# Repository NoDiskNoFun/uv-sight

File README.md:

# Anchored

**Anchored** is a bow sight add-on: automatic UV illumination, cant indicator and shot counter for a compound bow hunting sight. **Nocked** is its companion app, as a web app in this repository and as a native Android app in [uv-sight-android](https://github.com/NoDiskNoFun/uv-sight-android). The repositories keep their original name `uv-sight`.

> **Disclaimer: AI-generated project**
>
> The firmware, the web app, this README and the hardware design (part selection and wiring) were created with **Claude**, an AI assistant by Anthropic, in a conversation with the project owner.
>
> | | |
> |---|---|
> | Model | Claude Opus 5.5 (Anthropic) |
> | Interface | claude.ai, chat with code execution and web search |
> | Period | 23 September 2026, finished on 25 September 2026; reviewed and extended on 30 September 2026 |
> | Human role | Requirements and feature decisions, choice and purchase of parts, soldering and assembly, compiling and flashing, testing on the real bow, bug reports |
> | AI role | Part selection and wiring, all firmware and app code, protocol design, research of datasheets and pinouts, documentation |
> | Testing by the AI | Syntax and type checks of the firmware against mock libraries, JSON validity checks, and an end-to-end test of the app in Chromium against the firmware running natively with mocked IMU, flash and Bluetooth. The AI never ran the code on real hardware. |
> | Firmware / protocol / app | Firmware 7.6, protocol 24, app 5.23 |
>
> Several values in this project are estimates or were only checked in the field by the owner (runtimes, thresholds, shot detection). Treat them as starting points, not as guarantees. LiPo batteries can be dangerous if handled wrongly. Build and use this at your own risk.

---

## Contents

1. [Features](#features)
2. [Hardware](#hardware)
3. [Wiring](#wiring)
4. [Assembly and mounting](#assembly-and-mounting)
5. [Firmware: build and flash](#firmware-build-and-flash)
6. [Operation](#operation)
7. [Battery and charging](#battery-and-charging)
8. [Bluetooth commands](#bluetooth-commands)
9. [Settings reference](#settings-reference)
10. [Compile-time constants](#compile-time-constants)
11. [Web app](#web-app)
12. [JSON protocol (version 4)](#json-protocol-version-4)
13. [Troubleshooting](#troubleshooting)
14. [Known limitations](#known-limitations)

---

## Features

- **Automatic illumination:** The UV LED lights the sight's fluorescent fibre when it is dark and the bow is in use. Brightness is set in percent, either fixed or fading in with the dusk. It is held steady over the whole battery discharge via PWM.
- **Motion-based power management:** When the bow lies still, LED, light sensor and Bluetooth switch off, the accelerometer drops to 12.5 Hz and the board sleeps until the IMU reports motion on its interrupt line. Picking the bow up wakes it at once.
- **Cant indicator:** The LED blinks when the bow is canted sideways, faster the more it is tilted, or inverted: faster the closer to level. Aiming up or down does not count. Modes: off, auto (during a session) and on (always).
- **Shot counter:** Detects every shot through the impact on the riser (IMU tap detection via hardware interrupt). Shots are grouped into ends and training sessions.
- **Scoring:** Enter the scores of each end (0–10, X, M). Each end is checked against the counted shots. Sessions and their ends are stored on the board's 2 MB flash (room for about 32,000 records).
- **Battery:** USB-C charging at a fixed 50 mA, charge status, battery percentage and a deep-discharge cutoff for the LED.
- **Bluetooth:** Everything can be read and configured over Bluetooth LE (Nordic UART Service), either with a serial terminal app or with the included web app.
- **Web app (PWA):** Status, training keypad, history with chart, CSV export, backup and import, settings with guided calibration, automatic sync of sessions in both directions. Works offline once installed.
- **Aiming range (optional):** With the distance set per end, the sight learns which aiming angle belongs to which distance and can warn when the aim does not fit the distance. Several arrow/bow setups can be kept.
- **Update mode:** Reboot into the UF2 bootloader from the app, no double click on the reset button needed.

---

## Hardware

### Bill of materials

| # | Part | Type / value | Qty | Purpose |
|---|---|---|---|---|
| 1 | Microcontroller | Seeed Studio XIAO nRF52840 **Sense** | 1 | Control, Bluetooth, built-in LiPo charger (BQ25101), USB-C, 6-axis IMU (LSM6DS3TR-C) |
| 2 | LiPo battery | 3.7 V, 85 mAh, about 4 × 12 × 25 mm, with protection circuit | 1 | Power supply |
| 3 | UV LED | 5 mm, 390–405 nm (the owner reused the LED of the sight's original light, forward voltage measured 2.873 V at about 1 mA) | 1 | Lights the sight fibre, cant indicator |
| 4 | Resistor | 68 Ω, 1/4 W | 1 | LED current limit (about 16 mA peak at 4.2 V) |
| 5 | NPN transistor | BC547 (or BC337) | 1 | Switches the LED from the battery |
| 6 | Resistor | 2.2 kΩ, 1/4 W | 1 | Transistor base resistor |
| 7 | Photoresistor (LDR) | GL5528, 5 mm | 1 | Ambient light sensor |
| 8 | Resistor | 10 kΩ, 1/4 W | 1 | Voltage divider for the LDR |
| 9 | Wire | Thin flexible silicone wire, 2 cores, about 15–20 cm | 1 | Housing to LED in the sight |
| 10 | Heat shrink | Assorted sizes | – | Insulation, strain relief |
| 11 | Housing | Rigid, screwed to the riser | 1 | See [assembly](#assembly-and-mounting) |

No separate battery voltage divider, charger module or switch is needed: the XIAO board has a battery divider, charger and USB-C on board. Power management is done entirely in software.

### Why a transistor for the LED

A GPIO pin only delivers the regulated 3.3 V of the board. A UV LED needs about 3.0–3.4 V, which leaves nearly nothing for current regulation. The LED is therefore powered directly from the battery (3.4–4.2 V) and the GPIO only switches the transistor.

### Battery notes

- The battery used here has **three wires**. The third one is a temperature sensor (NTC). The XIAO has no pad for it: **cut it short and insulate it**, only plus and minus are connected.
- Use a cell with a built-in protection circuit. It is the last line of defence against deep discharge.

---

## Wiring

### Pin assignment

| Function | XIAO pin | nRF52840 | Notes |
|---|---|---|---|
| UV LED (PWM, via transistor) | D6 | P1.11 | Base of BC547 via 2.2 kΩ |
| LDR supply | D2 | P0.28 | Only HIGH during a measurement (saves power) |
| LDR measurement | D0 / A0 | P0.02 | Midpoint of the LDR divider |
| Battery voltage | internal | P0.31 | On-board divider 1 MΩ / 510 kΩ |
| Battery measurement enable | internal | P0.14 | Kept LOW permanently (must not be HIGH while charging) |
| Charge current select | internal | P0.13 | High-impedance input = 50 mA (set in code) |
| Charge status | internal | P0.17 | LOW = charging (board charge LED) |
| IMU interrupt INT1 | internal | P0.11 | Shot detection |
| IMU power | internal | P1.08 | Switched on by the firmware |

D1, D3–D5 and D7–D10 remain free.

### UV LED

```
BAT+ ---[68 Ω]--- LED anode (+, long leg) --- LED cathode (-, short leg) --- collector (C)
                                                                             BC547
D6 -----[2.2 kΩ]------------------------------------------------------------ base (B)

GND ------------------------------------------------------------------------ emitter (E)
```

BC547 pinout, flat side facing you, legs down: **C – B – E** from left to right. Check against the datasheet of your part.

### Light sensor

```
D2 ---[LDR GL5528]---+---[10 kΩ]--- GND
                     |
                     A0
```

The LDR has no polarity. Bright light means a high reading, darkness a low reading.

### Battery

```
Battery (+) --- BAT+ pad (bottom of the XIAO)
Battery (-) --- BAT- pad
Battery NTC (3rd wire) --- not connected, insulated
```

### Overview

```
                 +--------------------------------------+
   USB-C ------> |  XIAO nRF52840 Sense                 |
                 |   (charger, IMU, Bluetooth on board) |
                 |                                      |
   LiPo 85 mAh --| BAT+ / BAT-                          |
                 |                                      |
                 | D6 ---[2.2k]--- BC547 --- UV LED ----+---- to the sight (2-core wire)
                 | D2 ---[LDR]---+                      |
                 | A0 -----------+---[10k]--- GND       |
                 +--------------------------------------+
```

---

## Assembly and mounting

- **Mount the housing rigidly.** Shot detection relies on the impact travelling through the riser. Screw the housing on, ideally to an existing accessory thread. Foam double-sided tape and magnets dampen the impact and cause missed shots. Thin structural acrylic tape without a foam core is the fallback if screwing is impossible.
- **Orientation does not matter.** All three IMU axes are evaluated for shots, and the cant indicator is calibrated in place.
- **The LED sits in the sight,** the electronics in the housing, connected by thin silicone wire with strain relief. Mark the LED polarity before desoldering an original light.
- **Place the LDR so that no UV light from the sight falls on it,** otherwise the light could switch itself off.
- **Keep the transistor and the 68 Ω resistor in the housing,** not in the sight.

---

## Firmware: build and flash

### Setup (Arduino IDE)

1. Add this boards manager URL in the preferences:
   `https://files.seeedstudio.com/arduino/package_seeeduino_boards_index.json`
2. Install the board package **"Seeed nRF52 Boards"** (not the "mbed-enabled" variant).
3. Select the board **"Seeed XIAO nRF52840 Sense"**.
4. Install the library **"Seeed Arduino LSM6DS3"** via the library manager. Bluefruit and LittleFS are part of the board package.

### Setup (arduino-cli)

```sh
arduino-cli config add board_manager.additional_urls \
  https://files.seeedstudio.com/arduino/package_seeeduino_boards_index.json
arduino-cli core update-index
arduino-cli core install Seeeduino:nrf52
arduino-cli lib install "Seeed Arduino LSM6DS3"

arduino-cli compile --fqbn Seeeduino:nrf52:xiaonRF52840Sense path/to/uv_visier/
arduino-cli upload  --fqbn Seeeduino:nrf52:xiaonRF52840Sense -p /dev/ttyACM0 path/to/uv_visier/
```

The sketch file must have the same name as its folder, for example `uv_visier/uv_visier.ino`.

### Update mode (UF2)

Instead of double-clicking the reset button you can reboot the board into its UF2 bootloader:

- in the app: *Settings → Firmware and app → Update mode*, or
- in a terminal: send `dfu`.

The USB cable must be connected, otherwise the command is refused (the board would sit in the bootloader and drain the battery). The board appears as a USB drive. Copy a `.uf2` firmware onto it, or upload with the Arduino tools.

### What is stored in flash

| File | Where | Content | Saved |
|---|---|---|---|
| `/uvcfg.bin` | internal | Settings | With `save` |
| `/shotstate.bin` | internal | Shot counter on/off, log epoch, last session number | Automatically |
| `/level.bin` | internal | Cant indicator mode, calibration, LED switch, signals | Automatically |
| `/setups.bin` | internal | Arrow/bow setups (32 since 7.0, with their owner on a shared sight; the 8 of older firmware are taken over) | Automatically |
| `/group.bin` | internal | Shared sight: salted password hash, trainers, trainer requests | Automatically |
| `/badges.bin` | internal | Play-mode badges a trainer stored (rules only, up to 16) | Automatically |
| `/sightname.txt` | internal | Name of this sight (`name <text>`) | Automatically |
| `/sightid.bin` | internal | The sight's id after a factory reset (random; without the file the chip's own id is used) | At the factory reset |
| `/shotmodel.bin` | internal | Shot matching model per setup and its on/off switch (8 setups of older firmware are taken over) | Automatically |
| `/bathist.bin` | internal | Battery history for the runtime estimate | Automatically |
| session log | external 2 MB QSPI flash | Sessions and ends as 64-byte records with CRC, ring buffer | Automatically |
| `/shots.old` | internal | Backup of the log format of firmware 1.2 to 2.1 after the migration | Once |

`factory confirm` (asked for with `factory` first; in the apps under *Settings → Advanced settings → Factory reset*) erases all of it, the session log included, draws a new random id and restarts the sight: it is then as freshly flashed, and to the apps it is a new sight, so nothing the app holds about the old one (sessions, settings) is copied back. When a firmware update changes the layout of an internal file, that file starts over with defaults. The session log on the external flash keeps its format. Export a backup from the app before updating anyway.

---

## Operation

### Active and idle

- **Active:** The bow was moved within the timeout (default 5 min). LED logic, light sensor and Bluetooth run.
- **Idle:** The bow lies still. Everything is off. The IMU's interrupt line wakes the board when the bow moves; without motion it only wakes every 5 s for housekeeping. A Bluetooth connection is dropped when the board goes idle; a connection alone does not keep it awake. USB power or an `awake` hold from the app keep Bluetooth reachable without movement.
- A running session survives idle phases. It is only ended by `session_end` minutes without a shot, by `shots stop`, or by a restart of the board.

### Illumination

- In the normal mode (`mode auto`) the LED lights only while a session is running and it is dark. A session starts with the first shot the sight registers, or earlier with `shots start` (the app's *Start session*); so the first arrow of a session shot without starting it in the app is unlit. The cant blinking and the distance warning work with or without a session.
- Every 2 s the light sensor is read (0 = dark, 4095 = bright).
- `confirm` readings in a row are needed to switch. Right after picking up the bow the decision is immediate.
- **Brightness in percent** on a perceptual scale: 50 % looks about half as bright as 100 %. 100 % is 15 mA average, the former default of 5 mA is 61 %.
- **Fixed** (`bright_mode 0`): below `dark_on` the LED switches on with `bright`, above `dark_off` it switches off. The gap prevents flicker.
- **Auto** (`bright_mode 1`): getting darker, the LED comes on at `dark_off` with `bright_min` and gets brighter until it reaches `bright` at `dark_on`; below that it stays at `bright`. Getting brighter, it dims the same way and goes off above `dark_off`. The blend follows the light sensor logarithmically and glides over `fade` seconds instead of jumping.
- The brightness is kept steady by PWM (12 bit) as the battery voltage drops.
- Modes: `mode auto` (normal: dark and session), `mode on` (always on), `mode off` (always off). The mode is kept over restarts.

### Cant indicator

| | level | canted |
|---|---|---|
| bright | LED off | LED blinks |
| dark | LED on | LED blinks |

- Blinking uses `bright` minus `tilt_offset` percentage points (0 = same brightness), independent of the current auto brightness.
- **Style normal:** just outside the tolerance `blink_min` (1 Hz), from `tilt_full` (10°) on `blink_max` (8 Hz), in between the rate rises linearly.
- **Style inverted** (`level style inverted`): just outside the tolerance `blink_max`, from `tilt_full` on `blink_min`, so fast blinking means you are close to level. Within the tolerance the LED behaves as in normal style (on when dark, off when bright).
- The cant reading is smoothed over `tilt_smooth` against hand tremor. Leaving the tolerance switches at `level_tol`, returning at 70 % of it, so the edge does not flicker.
- A new rate takes effect at the start of the next blink cycle.
- Only sideways cant counts. Aiming up or down is ignored thanks to the two-step calibration.
- After a shot the indicator pauses for `lockout` (default 1.5 s).

| Mode | Command | Behaviour |
|---|---|---|
| Off | `level off` | No blinking |
| Auto | `level auto` | Only during a running session (needs `shots on`) |
| On | `level on` | Always while the bow is active |

**Calibration (once, saved immediately):**

1. Put the bow in a stand, level it with the bubble and aim horizontally. Send `level cal`.
2. Keep the bow level, but aim clearly up or down, at least 20°. Send `level cal2`.

Each step waits 3 s, then measures for about 0.6 s. If the two positions differ by less than 15°, step 2 has to be repeated.

### Shot counter, sessions and ends

- Turn the counter on with `shots on` (saved immediately).
- **Session start:** automatically with the first detected shot, or manually with `shots start`.
- **Shot detection:** The IMU reports impacts above `tap_ths` via interrupt. After a shot further impacts are ignored for `lockout`. Setting the bow down at the end often counts as a shot; this is handled below.
- **Ends:** Each `score` line closes an end and is compared with the shots counted since the last entry.
  - Match: the end is saved.
  - Mismatch: the device asks `save anyway? (yes/no/split)`. `yes` saves your values and your arrow count wins over the sensor count. `split` (offered when fewer values than shots were entered) saves the values as one end and keeps the remaining shots for the next end. `no` discards the input and the end stays open. Any command that changes the session or a setting also discards the input; commands that only read (`status`, `log …`, `level`, …) and the sync commands of the app leave the question open.
  - `score skip` closes an end without scores: it is stored as invalid, the sensor's arrow count is used, all arrows count 0 points and are left out of the average.
- **Scores:** `0`–`10` and `x` (inner ten: 10 points, counted separately). Several values per line, for example `score x 10 9 9 8 7`. If one value is invalid, the whole line is rejected. The app shows 0 as M (miss).
- **Session end:** automatically after `session_end` minutes (default 60) without a shot, or with `shots stop`. An open last end with exactly 1 shot is ignored (bow set down); with more shots it is stored as invalid. Sessions without any end are discarded.
- **Stored per session:** ends, shots, scored arrows, average, X count, duration in minutes, invalid ends and arrows, flags (corrected by hand, ended by hand). There is no clock on the board; the app derives the date.
- The log lives on the external flash and holds about 32,000 records; the oldest are overwritten when it is full. The app can delete single sessions or the whole log on the sight.

---

## Shot matching

With the shot counter running, the sight also records how the bow moved at each release and tells the app, per shot, where it expects the arrow relative to the end's mean: the height from the aiming angle, the sideways position from the bow's rotation in the last 30 ms before the impact (gyroscope, read from the IMU FIFO, shot mode only). The app matches these predictions to the arrow positions it sees on the photo and reports the sure pairs back (`shot teach`). From them, each setup learns its own factors and the remaining spread, so the predictions and the app's confidence improve with every end. Everything is stored per setup in `/shotmodel.bin`; `shot model` shows the state, `shot reset` starts over, `shot off` turns matching and the gyro off. The gyro adds about 0.5 mA while the bow is active.

## Shared sight (several archers, trainers)

A sight can be used by several archers in turn, for example in youth training, and watched by trainers. Nothing of this is active until an app names itself or a password is set; a sight used as before behaves as before.

- **Owner per session.** An app that greets with `app on <id> <name>` (a 16-digit hex id and a name of up to 12 characters) is the archer: every session that starts while it is connected carries that id and name (in the reserved bytes of the session record, `owner` / `ownerName` in `slot` and `session`). Sessions started without such an app have no owner.
- **Two links at once.** The sight accepts two Bluetooth connections. The archer's link is the primary one: it gets every live line (shots, status, events). A second link, a trainer looking in or a second archer, only gets the answers to its own commands, may only read (`status`, `shots`, `log …`, `setup`, `range`, `name`), end the session (`shots stop`) and, as a trainer, manage the group; anything that would disturb the archer answers `{"t":"err","code":"busy"}`. The second archer is told so in the greeting (`primary:false`). While a link is free the sight keeps advertising, so a trainer can always look in.
- **Password.** `group set <password>` (at least 4 characters) locks the sight: until a link sends `auth <password>` it answers only the greeting, `auth`, `group` and `time`, everything else with `{"t":"err","code":"auth"}`. The password is stored as a salted SHA-256 hash, never in clear; the link itself is not encrypted (no pairing), the password keeps strangers from reading the sessions. `group set -` removes it. Whoever sets the first password becomes the first trainer, provided the app named itself; a single-mode app (plain `app on`) may set a password too, and on a sight without trainers whoever gave the current password may change or remove it.
- **Roles.** `hello` and `auth` report the link's `role`: `none` (no id, as before), `open` (id, no password on the sight), `locked` (password not given yet), `user` (password given) or `trainer`. Users see their own sessions and those without an owner in `log since`, `log ends` and the setup list; trainers and single-mode apps see everything.
- **Trainers.** `group trainers` lists them (`trainersStart` / `trainer` / `trainersEnd`, `pending:true` for requests). A further trainer sends `group request` after `auth`; an existing trainer approves with `group approve <id>` or removes with `group remove <id>` (the last trainer only over USB). `group clear` wipes password and trainers and works over the USB console only, so nobody can take a sight over by radio.
- **Setups per archer.** On a shared sight every archer gets their own setup (named after them, created on the first greeting) and the sight switches to it when they connect, so the speed model and the shot matching learn per bow. There are 32 setups since 7.0.
- **Board data in the advertisement.** While it advertises, the sight puts manufacturer data (company id `0xFFFF`) into the packet: `"UV"`, version 1, flags (bit 0 session running, bit 1 password set, bit 2 session has an owner, bit 3 counter on, bit 4 a link is connected), battery %, end number, shots in the end, session points (16 bit), scored arrows, X count, the low 4 bytes of the chip id and the archer's name (8 bytes). A trainer's phone shows a whole range of sights from this without connecting. The 128-bit service UUID is no longer advertised (no room): apps find the sight by name and by this data.
- **Copying sessions in** (`log put …`) takes the owner as two optional trailing tokens, `<id> <name>`.
- **Badges.** A trainer stores the play-mode badges of the group on the sight: `badge set <id> <metric> <scope> <min|max> <l1>[,<l2>[,<l3>]] <emoji> <title>` (up to 16; id 8 characters, metric and scope as the app names them, one to three thresholds for bronze, silver and gold), `badge del <id>`, `badge clear`, `badge list` (`badgesStart` / `badgeItem` / `badgesEnd`). On a shared sight only a trainer writes. The sight stores the rules only; every archer's app fetches them on connecting and works out what it earned from its own history, and keeps what it earned even when a badge is removed again.

## Battery and charging

| Item | Value |
|---|---|
| Charge current | Fixed 50 mA (about 0.6 C for 85 mAh), about 2 h for a full charge |
| Charge termination | 4.2 V (charger chip) |
| LED cutoff | `cutoff`, default 3.40 V; released again at cutoff + 0.25 V |
| Percentage | 0 % = `cutoff`, 100 % = 4.2 V, following a typical LiPo curve |
| Charge status | `charging`, `full` (USB connected, done), `no USB` |

- While charging the voltage reads higher than at rest, so the percentage is optimistic. After charging a full cell settles to about 4.10–4.15 V.
- The ADC uses a 40 µs acquisition time because the on-board battery divider has a very high impedance. With the default 3 µs the voltage read about 0.1 V too low.
- The microcontroller keeps running below the cutoff; the battery's own protection circuit disconnects at roughly 2.5–3.0 V. The cutoff is what protects the cell from the LED.

### Runtime estimates

These are estimates, not measurements.

| Mode | Current (approx.) | Runtime with 85 mAh |
|---|---|---|
| Idle (bow lies still) | 0.04–0.08 mA | several weeks up to about 2 months |
| Active at night, LED at 61 % (5 mA) | about 6 mA | about 14 h |
| Active in daylight, training, no LED | 0.5–1 mA | several days |

Measurements taken with a USB power meter are not meaningful for battery runtime: with USB connected, the USB interface of the chip is active and the LED draws from the battery, not from USB.

---

## Bluetooth commands

Connect with any Nordic UART terminal (for example the Android app "Serial Bluetooth Terminal", line ending LF or CR+LF), with `ble-serial` on Linux, or with the web app. The board advertises as **Anchored** (**UV-Sight** before firmware 7.3) only while it is active.

| Command | Effect | Saved |
|---|---|---|
| `help` or `h` | List of commands | – |
| `status` or `?` | Current readings | – |
| `get` or `config` | All settings with range | – |
| `set <name> <value>` | Change a setting, active immediately | Only with `save` |
| `save` | Save settings to flash | Yes |
| `defaults` | Load default settings | Only with `save` |
| `factory`, then `factory confirm` within 30 s | Factory reset: erases every file above and the session log, gives the sight a new id and restarts. The sight is then as freshly flashed: no name, no password, defaults, and a new sight to the apps. On a shared sight trainers only. | – |
| `live on` / `live off` | Status every 2 s | No |
| `mode auto` / `on` / `off` | LED mode: on when dark during a session / always on / off | Yes |
| `shots` | Counter status and running session | – |
| `shots on` / `shots off` | Shot counter on/off (off only without a running session) | Immediately |
| `shots start` / `shots stop` | Start / end a session manually | Slot on end |
| `score 9 x 7 0` | Score an end | With the session |
| `score skip` | Close the end without scores (invalid) | With the session |
| `yes` / `no` | Answer a mismatch question | – |
| `log` | Stored sessions, 1 = newest | – |
| `level` | Cant indicator status | – |
| `level off` / `auto` / `on` | Cant indicator mode | Immediately |
| `level style normal` / `inverted` | Blink faster when tilted / when close to level | Immediately |
| `level cal` / `level cal2` | Calibration step 1 / 2 | After step 2 |
| `level signal on` / `off` | Blink when canted (measuring continues) | Immediately |
| `angle off` / `auto` / `on` | Measure the aiming angle at every shot | Immediately |
| `dist <m>` | Distance of the running session (0 = unknown); `score … @50` also sets it | With the session |
| `range`, `range signal on` / `off` | Learned distances and arrow speed; warning when the aim does not fit | Immediately |
| `setup`, `setup use` / `new` / `name` / `del` | Arrow/bow setups, each learns its own speed | Immediately |
| `log all`, `log since <n>`, `log ends <e> <id>`, `log info`, `log test` | Whole log, records after #n, ends of a session, flash status, flash self-test | – |
| `log put …`, `log putend …` | Write a session / end from a backup (used by the app); `log put` takes the owner as two trailing tokens | Yes |
| `log del <e> <id>`, `log clear confirm` | Delete one session / all sessions on the sight | Yes |
| `bat`, `bat reset` | Runtime estimate and measured current draw; clear the battery history | – / Yes |
| `time <unix> [tz]` | Set the clock (the app does this on every connect) | Until reboot |
| `awake <s>` | Stay reachable without movement, max 900 s | No |
| `app on` / `app off` | JSON output for the app / human-readable output | No (off on disconnect) |
| `app on <id> <name>` | As `app on`, naming the archer (16 hex digits, up to 12 characters); their sessions get this owner | No |
| `badge list`, `badge set …`, `badge del <id>`, `badge clear` | Play-mode badges stored on the sight, see above | Yes |
| `auth <password>` | Unlock a shared sight for this link | No |
| `group`, `group set <password>` / `-`, `group trainers`, `group request`, `group approve <id>`, `group remove <id>`, `group clear` (USB only) | Shared sight: password and trainers, see above | Yes |
| `name [text]`, `name -` | Name this sight (max. 16 characters); it appears in the app and behind "Anchored" in the Bluetooth name. `-` removes the name. The app also receives the sight's id (the chip's own, a new random one after a factory reset), so two sights are told apart even without a name | Yes |
| `shot list [m]` | Shots of the open end, one line each (`shotsStart`, `shotItem`…, `shotsEnd`): time, aiming angle, hold spread and duration, sinking before release, cant, bow rotation at release and the model's predicted position. The same lines follow every closed end | – |
| `shot trace [last] <i>` | Aim trace of one shot: angle and cant over the 1.9 s before the release, sent as `trace` lines of 8 samples each (`k` = index of the first, `n` = total) | – |
| `shot teach <end> <i>:<dx>:<dy> …` | Confirmed arrow positions (mm from the group's mean) for shots of the last closed end: the model learns from them | Yes |
| `shot model`, `shot reset [id]`, `shot on`/`shot off` | Shot matching model of the active setup: state, reset, switch (off also turns the gyro off) | Yes |
| `dfu` | Reboot into update mode (USB needed) | – |

Range is about 10 m at the default `tx_power` of 0 dBm; +8 dBm roughly doubles it. A cheap USB adapter without antenna, a metal PC case or a nearby USB 3 port can reduce the range a lot. Anyone within range can connect; there is no PIN.

---

## Settings reference

Change with `set <name> <value>`, keep with `save`. Out-of-range values are rejected. Settings saved by firmware before 1.8 in mA (`ma`, `tilt_ma`) are converted to percent automatically on the first start.

| Name | Meaning | Unit | Default | Min | Max |
|---|---|---|---|---|---|
| `dark_on` | Fixed: light on below. Auto: full brightness from here down | 0–4095 | 900 | 0 | 4095 |
| `dark_off` | Fixed: light off above. Auto: light starts here with `bright_min` | 0–4095 | 1200 | 0 | 4095 |
| `confirm` | Consecutive readings (2 s each) before switching | count | 2 | 1 | 10 |
| `bright_mode` | 0 = fixed, 1 = auto (fades with the light sensor) | – | 0 | 0 | 1 |
| `bright` | Brightness (fixed), or at `dark_on` and darker (auto) | % | 61 | 1 | 100 |
| `bright_min` | Auto: brightness at `dark_off`, where the light starts | % | 25 | 1 | 100 |
| `tilt_offset` | Cant blinking: percentage points below `bright` | % | 32 | 0 | 99 |
| `fade` | Auto: time to follow a change in darkness, 0 = instant | s | 5 | 0 | 30 |
| `tilt_full` | Cant at which the blink rate reaches its end value | degrees | 10.0 | 1 | 30 |
| `blink_min` | Slow blink rate (normal: just outside the tolerance) | Hz | 1.0 | 0.5 | 12 |
| `blink_max` | Fast blink rate (normal: from `tilt_full` on); above ~10 Hz it looks steady | Hz | 8.0 | 0.5 | 12 |
| `tilt_smooth` | Smoothing of the cant reading against hand tremor | ms | 400 | 50 | 2000 |
| `session_end` | Minutes without a shot until the session ends | min | 60 | 5 | 480 |
| `vf` | Forward voltage of the UV LED (for the brightness control) | V | 3.00 | 2.50 | 3.60 |
| `cutoff` | Battery cutoff for the LED, equals 0 % | V | 3.40 | 3.00 | 3.70 |
| `level_tol` | Cant tolerance | degrees | 1.0 | 0.2 | 10 |
| `tap_ths` | Shot threshold | × 0.25 g | 20 (5 g) | 1 | 31 |
| `ths` | Wake-up motion threshold | × 125 mg | 1 | 1 | 63 |
| `lockout` | After a shot: no counting, cant indicator paused | ms | 1500 | 200 | 5000 |
| `timeout` | Time without movement until idle | s | 300 | 10 | 3600 |
| `report` | Automatic status while connected, 0 = off. A status the app asks for restarts this timer, so polling and reports do not double up | s | 10 | 0 or 2 | 600 |
| `tx_power` | Bluetooth transmit power, rounded to −20, −16, −12, −8, −4, 0, 2…8 | dBm | 0 | −20 | 8 |
| `bat_mah` | Battery capacity, for the runtime estimate | mAh | 85 | 10 | 5000 |

**Calibrating the light thresholds:** at dusk send `live on`, watch the `Light=` value, set `dark_on` where the fibre no longer glows by itself and `dark_off` about 300 higher. Then `live off` and `save`.

**Calibrating the shot threshold:** every detected shot is reported. Shoot a few arrows and carry the bow around. Lower `tap_ths` if shots are missed, raise it if carrying counts as a shot. Then `save`.

---

## Compile-time constants

`UV_HAS_LED` (default 2): whether the UV LED stage (BC547, resistors, LED, light sensor) is fitted. 0 = no, for a sight on a bow without a pin, e.g. a hunting bow, that only counts shots and measures angles; 1 = yes; 2 = find out at boot. The check charges the LED pin and lets it float for a moment: with the transistor and its base resistor fitted the pin falls to the base-emitter voltage, without them it stays high. Without the LED stage the light settings default to off, the light sensor is not read, `mode on`, `level signal on` and `range signal on` are refused, and the app hides all light options (the `hello` message carries `"led":false`). Set it on the command line with `--build-property compiler.cpp.extra_flags=-DUV_HAS_LED=0`.

These are set at the top of the sketch and need a rebuild.

| Constant | Value | Meaning |
|---|---|---|
| `BRIGHT_MAX_MA` | 15 mA | LED current at 100 % |
| `BRIGHT_GAMMA` | 2.2 | Perceptual curve from percent to current |
| `PWM_BITS` | 12 | PWM resolution for fine steps at low brightness |
| `MAX_SCORES_LINE` | 40 | Maximum values per `score` line |
| `TILT_HYST_FRAC` | 0.3 | Hysteresis at the tolerance edge as a share of `level_tol` |
| `CAL_MIN_ANGLE_DEG` | 15° | Minimum angle between the calibration steps |
| `CAL_COUNTDOWN_MS` | 3000 ms | Wait before a calibration measurement |
| `SENSOR_INTERVAL_MS` | 2000 ms | Light and battery reading interval |
| `ACTIVE_POLL_MS` / `LEVEL_LOOP_MS` | 250 / 30 ms | Loop interval active / with cant indicator or aiming angle |
| `IDLE_WAKE_MAX_MS` / `IDLE_POLL_MS` | 5000 / 500 ms | Idle: longest sleep between housekeeping passes (the IMU interrupt ends it earlier) / poll interval if the board package has no INT1 pin |
| `TWIM_ANOMALY_89` | 1 | nRF52840 erratum 89 workaround (I2C peripheral off between loop passes): 0 = never, 1 = automatic (the firmware asks the Nordic MDK whether the chip revision is affected; only Engineering A is), 2 = always. `bat` shows whether it is active |
| `ADV_FAST_INTERVAL` / `ADV_SLOW_INTERVAL` | 100 ms / ~1 s | Advertising for the first 10 s / afterwards |
| `CONN_INT_MIN` / `CONN_INT_MAX` | 200 / 400 ms | Requested connection interval |
| `BLE_NAME` | `Anchored` | Bluetooth name |

---

## Web app

### Files

All six files belong in one folder:

```
index.html
sw.js
manifest.webmanifest
icon-192.png
icon-512.png
icon-maskable-512.png
```

The main file must be named exactly `index.html`.

### Hosting and installing

Web Bluetooth only works in **Chrome** and only on pages loaded via **https** or **localhost**. Opening the file directly from storage does not work.

- **Online Version**: [https://nodisknofun.github.io/uv-sight/](https://nodisknofun.github.io/uv-sight/)
- **Local server on the phone:** serve the folder with a local web server app and open `http://localhost:8080/`.
- **GitHub Pages:** create a repository, upload the six files, enable *Settings → Pages* for the `main` branch. The app is then at `https://<user>.github.io/<repo>/`.
- **Own server:** any static https web server.

Open the app once completely, then install it via *Settings → Install app* or the Chrome menu. After that it starts from the home screen without internet. When the server is reachable it loads updates automatically (network first, cached copy after 2.5 s).

If the device chooser stays empty, give Chrome the permission *Nearby devices* (Android 12 and later) or *Location* (older Android).

### Tabs

- **Status:** battery ring with percentage and voltage, session, UV light with brightness and mode (fixed/auto), ambient light, cant with mode and style, charging, and runtime estimates with light and resting. Refreshes every 5 s while open.
- **Runtime estimate:** remaining capacity (battery capacity × percentage) divided by an estimated current: LED at `bright` plus about 0.6 mA for the awake board, 0.2 mA each for shot detection and the cant indicator when switched on; resting about 0.06 mA. In auto mode the estimate assumes full brightness. Set the battery capacity under *Settings → Firmware and app* (default 85 mAh, stored on the phone).
- **Training:** current end with live shot count, session statistics, keypad in target ring colours (`1 2 3 / 4 5 6 / 7 8 9 / 10 X M`, undo), save end, skip end, end session. Scoring works without a connection; Save, Skip and End reconnect automatically (up to 10 s) and keep your entries if the sight is out of range. Entries survive an app restart. Mismatch questions appear as a dialog; *Edit scores* keeps your entries for correction.
- **History:** sessions from the device are archived on the phone without duplicates, with date, chart of the average and CSV export. Removing an entry only affects the phone.
- **Dates:** the sight has no clock. The app takes the date from the phone: when a session ends while connected, from `ago` when fetched later, or from the start time it remembered while it saw the session running. Only if the app was never connected during a session and the sight restarted before the session was fetched, the list shows "Before <fetch time>".
- **Settings:** battery capacity for the estimate, shot counter, cant indicator (off/auto/on) and blink style (normal/inverted), LED test, brightness mode (fixed/auto), all settings grouped with slider, number field, description, default and range, save bar, restore defaults, guided cant calibration, update mode, install button, versions.
- **Console:** raw lines and free command input for troubleshooting.

The archive is stored in Chrome's site data. Clearing Chrome's site data deletes it; export CSV now and then as a backup.

---

## JSON protocol (version 24)

After `app on` the device sends **only JSON, one object per line**, until `app off` or disconnect. Commands stay the same text commands. Every object has a type field `t`. Lines that do not start with `{` (for example the greeting before `app on`) can be ignored.

On `app on` the device sends `hello`, the settings (`cfgStart`, `cfgItem` …, `cfgEnd`), `status`, `session`, `level`, `loginfo`, `range` and the setups (`setupsStart`, `setupItem` …, `setupsEnd`).

| Type | Fields | Sent |
|---|---|---|
| `hello` | `proto`, `fw`, `name`, `imu`, `log`, `twim89`, `id`, `sname`, `led`, `pw` (password set), `role`, `pending`, `primary` | On `app on`; a locked link gets nothing else until `auth` |
| `auth` | `ok`, `role`, `pending` | Answer to `auth` |
| `group` | `pw`, `trainers`, `waiting`, `role`, `pending` | On `group`, after a change |
| `trainersStart` / `trainer` / `trainersEnd` | `n`; per trainer `id`, `name`, `pending` | On `group trainers`, after a change |
| `badgesStart` / `badgeItem` / `badgesEnd` | `n`; per badge `id`, `emoji`, `title`, `metric`, `scope`, `op`, `levels` | On `badge list`, after a change |
| `status` | `light`, `dark`, `vbat`, `pct`, `chg` (`charging`/`full`/`no USB`), `led` (`on`/`off`/`blinking`/`warning`/`pulsing`), `duty` (0–4095), `bright` (%), `mode`, `lowbat`, `tilt` (degrees or `null`), `session`, `awake`, `rwarn`, `lastShotG`, `lastShotClip`, `end`, `endShots` | On `status`, with `live on` every 2 s, every `report` s |
| `bat` | `light`, `rest` (hours), `full` (minutes or `null`), `src` (`measured`/`estimate`), `idleMa`, `activeMa`, `ledK`, `cap` | With every status |
| `cfgStart` | `n` | Start of the settings list |
| `cfgItem` | `k`, `v`, `def`, `min`, `max`, `dec`, `zero`, `unit`, `d` | One per setting |
| `cfgEnd` | – | End of the settings list |
| `session` | `counter`, `active`; if active also `epoch`, `nextId`, `dist`, `distSrc`, `end`, `endShots`, `ends`, `invalidEnds`, `shots`, `scored`, `sum`, `x`, `avg`, `min`, `pending`, `owner`, `ownerName` | On `shots`, after every change |
| `shot` | `end`, `endShots`, `total`, `g`, `clip`, `ang`, `cant` | Every detected shot |
| `end` | `n`, `valid`, `arrows`, `dist`, `distSrc`, `setup`, `ang`, `angSd`, `angN`, `cant`, `cantMax`, `canted`, `cantN`, `stored`; valid: `sum`, `x`, `avg`; invalid: `reason` | An end was closed |
| `confirm` | `end`, `counted`, `entered`, `split` | Mismatch, answer with `yes`, `no` or `split` |
| `discarded` | `end` | Input discarded, end still open |
| `sessionEnd` | `manual`, `stored`, `epoch`, `id`, `seq` (0 if not stored), `error` | Session ended (`stored:false` for empty sessions or a flash error); a `slot` line with the details follows |
| `logStart` | `since`, `last`, `total`, `epoch` | Start of a log answer |
| `slot` | `seq`, `epoch`, `id`, `start`, `ago`, `ends`, `shots`, `scored`, `avg`, `x`, `min`, `invalidEnds`, `invalidArrows`, `mismatch`, `manual`; `owner`, `ownerName` when the session has an archer | One per stored session |
| `endrec` | `seq`, `epoch`, `id`, `n`, `valid`, `arrows`, `skipped`, `sum`, `x`, `dist`, `auto`, `setup`, `ang`, `angSd`, `angN`, `cant`, `cantMax`, `canted`, `cantN`, `scores` | One per stored end |
| `logEnd` | `last`, `n` (records sent in this answer) | End of a log answer. The app compares `n` with what it received and asks again if a line was lost |
| `loginfo` | `ok`, `jedec`, `count`, `capacity`, `last`, `clock`, `migrated`, `error`, `initErr`, `resets` | On `log info` and `app on` |
| `range` | `setup`, `name`, `state` (`learning`/`anchor`/`ready`), `ends`, `dists`, `min`, `max`, `speed`, `kmh`, `drag`, `dist`, `distSrc`, `estimated`, `signal`, `warn`, `ok` | On `range`, after changes |
| `setupsStart` / `setupItem` / `setupsEnd` | `active`; per item `id`, `name`, `owner` (shared sight), `deleted`, `state`, `ends`, `kmh`, `min`, `max` | On `setup`, after changes |
| `logtest` | `step`, `ok`, `detail` | During `log test` |
| `level` | `mode` (`off`/`auto`/`on`), `style` (`normal`/`inverted`), `cal`, `angle` (`off`/`auto`/`on`), `cantSignal`, `rangeSignal` | On `level`, after changes |
| `cal` | `step`, `state` (`countdown`/`ok`/`error`), `text` | During calibration |
| `event` | `e`: `idle`, `lowbat`, `charge` (+`state`), `light` (+`dark`), `range` (+`warn`: `low`/`high`/empty, `ok`) | Device events. `range` is sent whenever the aiming-range signal changes, so an app can mirror the LED (e.g. by vibrating) |
| `ack` | `cmd`: `set` (+`k`, `v`), `save`, `live` (+`on`), `mode` (+`mode`), `dfu`, `dist`, `awake`, `time`, `batreset`, `setup` (+`ok`, `id`), `put` / `putend` (+`result`), `del` (+`result`), `clear` (+`ok`, `count`), `factory` (+`armed` / `ok`, `id`, `newId`), `group` (+`what`, `pw` / `id` / `pending`), `badge` (+`what`, `id`) | Confirmation of a command |
| `err` | `text` | Error |
| `msg` | `text` | Any other human-readable message |

**Session identity:** `epoch` is a random number of the log, newly created whenever the log starts empty. `id` is a running session number. `epoch` + `id` identify a session uniquely. A running session already reports the key it will get (`epoch` + `nextId`). `seq` is the write number of a record on the flash; the app remembers the newest `seq` it has and asks for `log since <seq>`. `start` is the unix time of the session start if the app had set the clock, `ago` the number of minutes since the session was saved, or `null` after a reboot of the board.

**Why short lines:** long lines (about 1,500 characters) were lost or corrupted over Bluetooth in practice. The settings are therefore sent as one short line per item. No line is longer than about 350 characters.

---

## Troubleshooting

| Problem | Cause and fix |
|---|---|
| App or terminal does not find `Anchored` | The board is idle. Move the bow, then search within 10 s. |
| PC finds the sight only briefly or not at all | Weak adapter: use a USB extension cable, avoid USB 3 ports, or raise `tx_power`. On Linux connect directly with `ble-serial -d <MAC> -t 15`; pairing is not needed. |
| Connection drops | After `timeout` without movement the board disconnects on purpose. Move the bow or raise `timeout`. |
| Settings tab says "Loading settings…" for long | Lines got lost. The app retries three times; move closer and tap *Try again*. |
| Protocol warning in the app | Firmware and app versions do not match. Update both. |
| Status reports keep coming after `live off` | That is the periodic `report`. Set `report 0` to switch it off. |
| Linker error about `GPIOTE_IRQHandler` | The sketch owns the GPIOTE interrupt for the IMU line. Nothing else in the sketch may call `attachInterrupt`. |
| LED switches nervously at dusk | Raise `confirm` or widen the gap between `dark_on` and `dark_off`. |
| Fibre too bright in full darkness | Lower `bright`; in auto mode it applies from `dark_on` down. |
| Shots are not counted | Check `shots` is on and the housing is screwed rigidly. Lower `tap_ths`. |
| Carrying the bow counts as a shot | Raise `tap_ths`. Setting the bow down at the end of a session is handled automatically. |
| Cant indicator never blinks | Check `level`: mode, calibration, and in auto mode a running session. |
| Cant blinks although the bubble is centred | Repeat the calibration or raise `level_tol`. |
| Battery percentage too high while charging | Normal, read it some minutes after unplugging. |
| LED stays off, "BATTERY EMPTY" | Deep-discharge protection. Charge the battery. |
| Settings lost after restart | `save` was missing, or the settings layout changed with a firmware update. |
| Compile error "does not name a type" | Arduino generates function prototypes before the first function; all types must be defined above it. Keep the order of the sketch. |
| Warning "PIN_LSM6DS3TR_C_INT1 not defined" | Board package without the interrupt pin; shot detection falls back to polling and may miss shots. |

---

## Known limitations

- **No clock:** sessions have no timestamp on the device. Dates come from the phone and are only approximate ("Before …") if the app never saw the session running and the sight restarted before it was fetched.
- **Shot detection by impact threshold:** setting the bow down hard can count as a shot. The threshold has to be tuned per bow and mounting position.
- **No Bluetooth security:** anyone in range can connect and change settings while the bow is active.
- **Cold:** below 0 °C LiPo capacity drops noticeably; runtime will be shorter than estimated.
- **Estimates:** runtimes and some thresholds are estimates and were not measured by the author of the code.
- **Web Bluetooth:** only Chrome on Android is supported; iPhone browsers do not support Web Bluetooth.
- **Erratum 89 of the chip:** the nRF52840 erratum that adds up to about 0.4 mA while the I2C peripheral stays enabled next to GPIOTE only affects the revision Engineering A, which no XIAO board carries. The firmware checks the revision at start and applies the workaround only there (`TWIM_ANOMALY_89`).

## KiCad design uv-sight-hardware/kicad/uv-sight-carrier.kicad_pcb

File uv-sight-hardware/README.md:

# UV-Sight Hardware

Carrier board and 3D-printed case for **UV-Sight**: automatic UV illumination, cant indicator and shot counter for a compound bow sight, built around a Seeed Studio XIAO nRF52840 Sense.

> **AI-generated design.** The board layout, schematic, case modifications and this guide were created with Claude (Anthropic) together with the project owner. The design has been checked with KiCad's design rule check and against the 3D models, but **it has not been built and tested on real hardware yet.** Build at your own risk. LiPo batteries can be dangerous if handled wrongly.

---

## What's in this folder

| Folder / file | What it is | Do you need it? |
|---|---|---|
| `gerber/uv-sight-carrier_gerber.zip` | Manufacturing files for the board | **Yes**: upload this zip to a PCB maker |
| `3d-print/case.stl` | Case, fits the bow mount | **Yes**: print it |
| `3d-print/shim.stl` | 1.2 mm spacer between battery and board | **Yes**: print it |
| `3d-print/header-spacer.stl` | 1.5 mm strip that lifts the XIAO on its pin header | **Yes**: print it **twice** |
| `3d-print/rail-test/` | Four short test pieces to find the right rail fit for your printer | Recommended |
| `docs/` | Assembly drawing, VBAT wire drawing, schematic (PDF), mount fit | Read while building |
| `kicad/` | KiCad project (schematic and board) | Only if you want to change the design |

---

## 1. Order the board

Upload `gerber/uv-sight-carrier_gerber.zip` to any PCB maker (JLCPCB, PCBWay, Aisler and others). Use these settings:

| Setting | Value |
|---|---|
| Layers | 2 |
| Size | 26.4 × 19.4 mm |
| Thickness | **1.6 mm** (the height of the case is calculated with 1.6 mm) |
| Surface finish | HASL lead-free or ENIG |
| Colour | any |

Minimum track width 0.3 mm, minimum clearance 0.2 mm and minimum drill 0.3 mm are standard at every maker.

## 2. Print the parts

**Material: PETG** (or ASA if your printer has an enclosure). Do not use PLA. It softens at about 55 °C, for example in a car in summer, and becomes brittle in the cold.

- Use an **opaque, dark** filament. Translucent plastic lets light through the walls onto the light sensor and spoils the light reading.
- Layer height 0.12–0.16 mm, at least 5 perimeters (the 2 mm walls come out solid).
- Print the case with the open side up.

**Rail fit:** the rails on the sides of the case slide into the bow mount. Printers differ, so first print the four pieces in `3d-print/rail-test/`, **in the same material as the case**. They have 0.10, 0.15, 0.20 and 0.25 mm less material on each face of the rail. The number of notches on top of one wall tells you which is which (1 notch = 0.10 mm, 4 notches = 0.25 mm). Pick the one that slides in with a little force. `case.stl` uses **0.15 mm**. If you need another value, the case has to be regenerated with that value.

## 3. Parts list

| Ref | Part | Qty | Notes |
|---|---|---|---|
| U1 | Seeed Studio XIAO nRF52840 **Sense** | 1 | |
| – | Pin header 1×7, 2.54 mm | 2 | connects the XIAO to the carrier board |
| – | `header-spacer.stl`, printed | 2 | lift the XIAO to 4 mm above the board so the resistors fit underneath |
| R1 | Resistor 68 Ω, 1/4 W | 1 | LED current |
| R2 | Resistor 2.2 kΩ, 1/4 W | 1 | transistor base |
| R3 | Resistor 10 kΩ, 1/4 W | 1 | light sensor divider |
| Q1 | BC547 (or BC337), TO-92 | 1 | |
| R4 | Photoresistor GL5528, 5 mm, leaded | 1 | |
| J1 | LiPo 3.7 V, 85 mAh, about 4 × 12 × 25 mm, **with protection circuit** | 1 | wires soldered to J1 |
| J3 | UV LED 5 mm, 390–405 nm, on a 2-wire cable | 1 | sits in the sight |
| – | Micro-JST 1.25 mm 2-pin plug + socket with wires (PicoBlade compatible, about 4 × 3 mm) | 1 pair | LED cable through the case wall |
| – | Thin insulated wire, e.g. 30 AWG wire-wrap wire | ~2 cm | **VBAT wire** (see step 6) |
| – | Double-sided tape without foam core, e.g. 3M 467MP | – | holds battery, shim and board |
| – | Pin header 2×4 or wires (optional) | 1 | display connector J2 |

## 4. Build the board

The order matters: the XIAO covers everything below it once it is soldered in.

1. **Resistors R1, R2, R3.** Insert them from the top, lying flat; the values are printed on the board. Solder them on the bottom and cut the leads short.
2. **Light sensor R4 (LDR).** Insert it **from the bottom**, so its head is on the battery side, and solder it on the top. **Keep the legs long**: the head has to reach down into the hole in the case floor, about 6 mm below the board. Bend it to height later in the case.
3. **Transistor Q1.** Insert it from the top, standing, **flat side facing the XIAO**. The collector goes into the square pad. Solder it on the bottom.
4. **Battery wires (J1).** Insert them from the bottom and solder them on the top. **BAT+ goes into the square pad.** The battery's third wire (temperature sensor) is not used: cut it short and insulate it.
5. **LED cable (J3).** Use the JST pigtail. Insert it from the top and solder it on the bottom. **LED+ (anode, long LED leg) goes into the square pad.** Leave some slack inside the case and tie a knot in the cable as strain relief.
6. **VBAT wire.** This is the only tricky step; see the drawing above.
   - **Why it is needed:** the XIAO takes battery power only from a small **BAT+** pad on its **underside**, not from a header pin. The LED also needs battery voltage, so a short wire brings BAT+ from that pad down to the carrier board, into the hole marked **VBAT**.
   - **a)** Turn the bare XIAO upside down. Find the two pads in the middle: **BAT+** is about 10 mm from the USB-C end and about 4.4 mm from the D0–D6 edge. Solder about 15 mm of thin insulated wire to it, pointing straight away from the board. Leave the BAT− pad next to it empty: it is ground and is already connected through the GND header pin.
   - **b)** Put both 1×7 pin headers into the carrier board, long pins up, and slide a printed `header-spacer` over the pins of each header, on top of the black plastic. Set the XIAO onto the pins with USB-C at the end **opposite** J2, and **thread the wire through the VBAT hole** as you do. Solder the XIAO to the pins on top, then the pins on the bottom.
   - **c)** From the bottom, pull the wire straight, solder it into the VBAT hole and cut off the rest.
7. **Bottom side.** Cut all lead ends as short as possible with flush cutters.
8. **Check before connecting anything:** with a multimeter, make sure there is **no short between BAT+ and BAT−** on J1, and that the VBAT hole is connected to BAT+.

## 5. Put it into the case

1. **Battery:** stick it flat onto the case floor with tape, in the corner away from the hole in the floor.
2. **Shim:** tape `shim.stl` onto the battery. The solder joints on the bottom of the board sit in the cut-outs of the shim. **Never let solder joints touch the LiPo**: a sharp lead can pierce the pouch and short the cell.
3. **Board:** tape the board onto the shim, USB-C towards the wide cut-out. Bend the LDR so that its head sits in the floor hole.
4. **JST connector:** press it into the slot at the top of the end wall opposite USB-C. The slot is made to the plug's measured size of 4.0 × 3.0 mm; file it if it is too tight. Fix it from inside with a little hot glue.

**Never solder on the board while the battery is attached underneath.**

The stack is about 15.3 mm high, and the case is 16 mm high inside.

## 6. Bow mount

The mount has a closed roof (it closes the open top of the case) and a closed back wall. Slide the case in **USB-C end first**, so that the **LED/JST end faces the open front**. The case floor sticks out of the mount by 1 mm, so you can grip it with your fingers to pull the case out, for example for charging.

The rails are at the same height as in the original case, so the case fits the existing mount.

---

## Reference

### Wiring

The wiring is the same as in the UV-Sight firmware README (firmware 5.8):

| Function | XIAO pin |
|---|---|
| UV LED, PWM through Q1 | D6 |
| LDR supply (HIGH only while measuring) | D2 |
| LDR measurement | A0 / D0 |
| Battery | BAT+ pad (via the VBAT wire), GND |

Full schematic: [docs/schematic.pdf](docs/schematic.pdf)

### J2: display / expansion connector

Eight holes behind the XIAO, directly below the LED pads. Pin 1 is the square pad.

```
 1  3V3          2  GND
 3  D7           4  D8  (SPI SCK)
 5  D9 (MISO)    6  D10 (SPI MOSI)
 7  5V           8  GND
```

- **SPI display:** fits directly. Use SCK = D8 and MOSI = D10; CS and DC on D7 and D9, for example.
- **I²C display:** the XIAO's default I²C pins D4 (SDA) and D5 (SCL) are on the other header row and are not on J2. Solder to the XIAO's header pins, or move I²C in the firmware.
- **5V** only exists while USB is plugged in. Power a display from 3V3.

### Opening the KiCad project

Open `kicad/uv-sight-carrier.kicad_pro` with KiCad 7 or newer. The project brings its own library for the XIAO footprint and the wire pads (`kicad/lib`); everything else comes from KiCad's standard libraries.

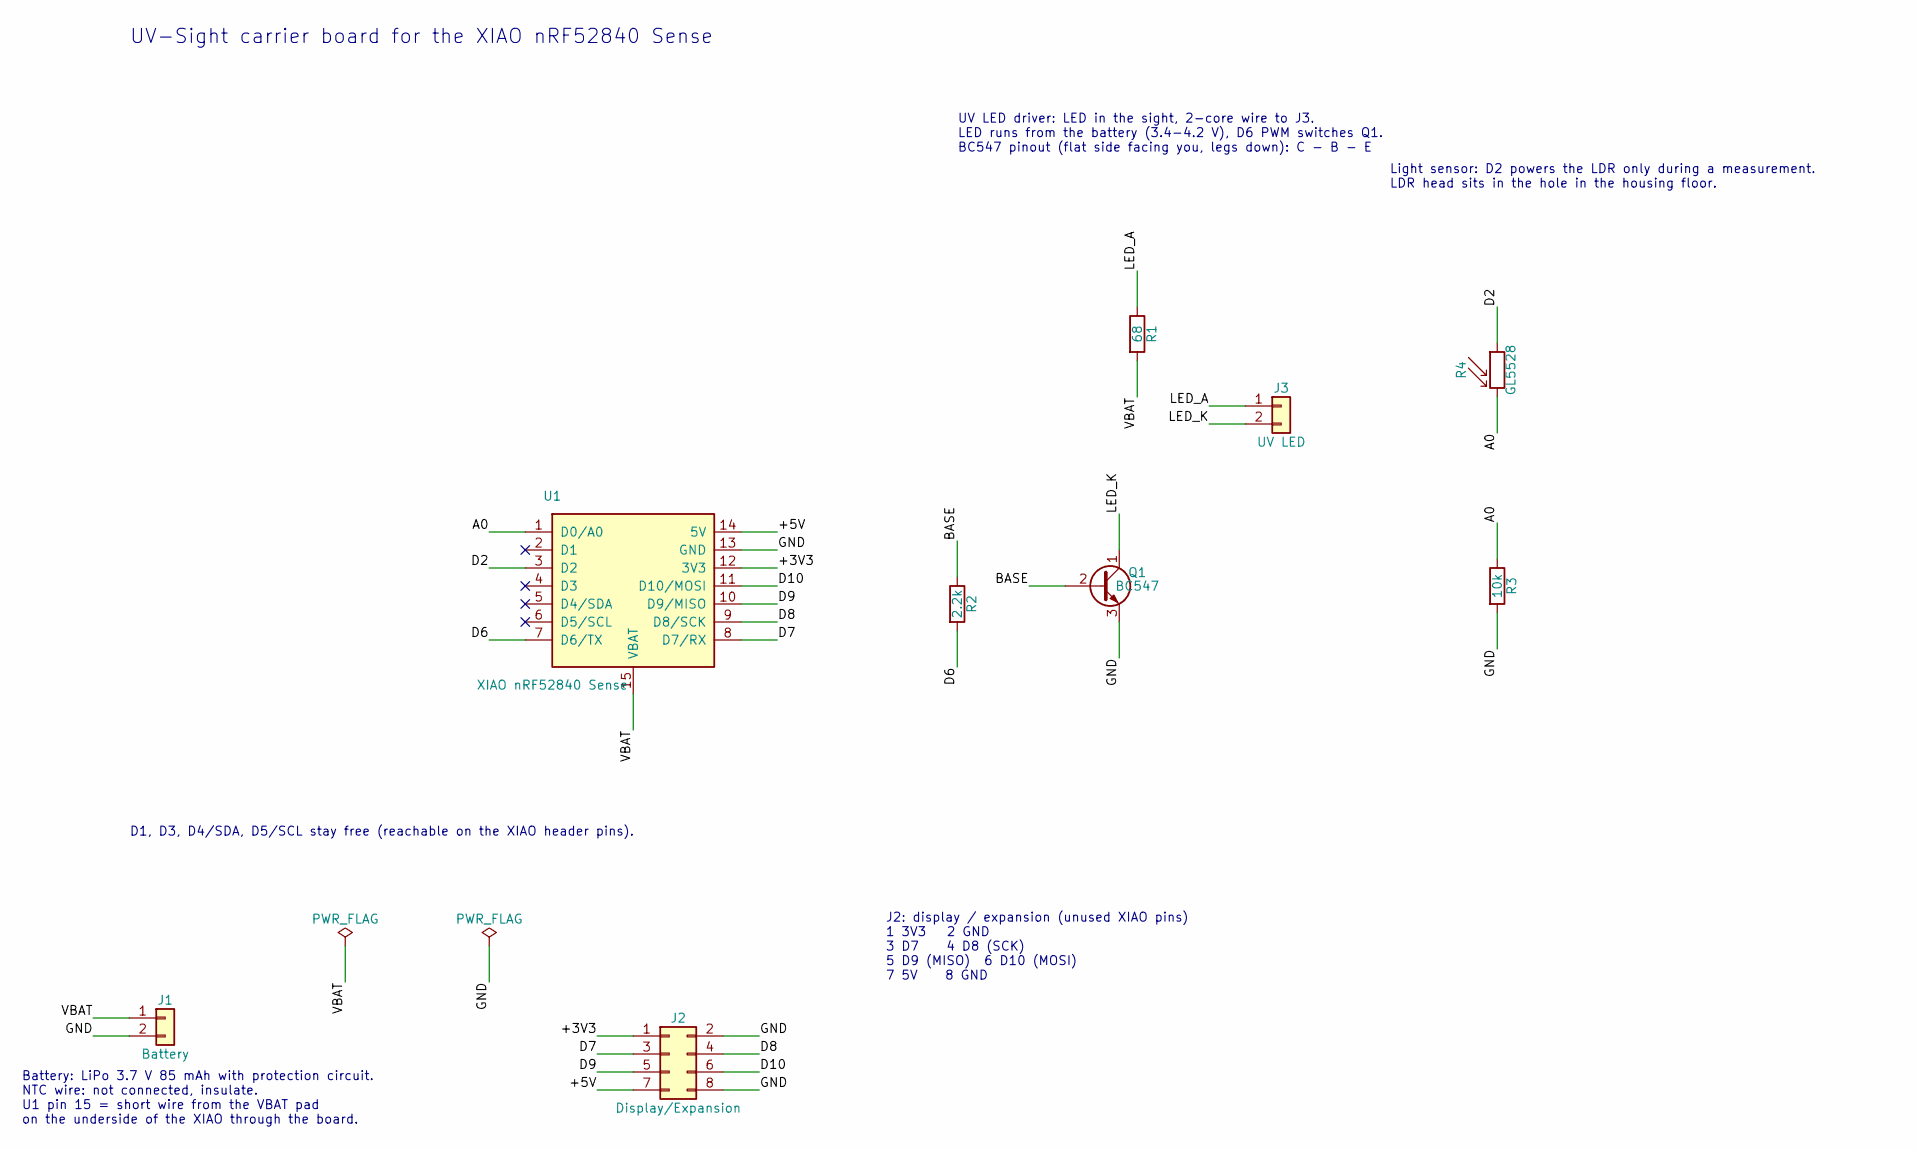
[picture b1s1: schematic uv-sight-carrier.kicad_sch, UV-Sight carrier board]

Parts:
J1: Battery; WirePad_1x02_P2.54mm
J2: Display/Expansion; PinHeader_2x04_P2.54mm_Vertical
J3: UV LED; WirePad_1x02_P2.54mm
Q1: BC547; TO-92_Inline
R1: 68; R_Axial_DIN0207_L6.3mm_D2.5mm_P10.16mm_Horizontal
R2: 2.2k; R_Axial_DIN0207_L6.3mm_D2.5mm_P10.16mm_Horizontal
R3: 10k; R_Axial_DIN0207_L6.3mm_D2.5mm_P10.16mm_Horizontal
R4: GL5528; R_LDR_5.1x4.3mm_P3.4mm_Vertical
U1: XIAO nRF52840 Sense; XIAO_nRF52840_Header_VBAT

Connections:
+3V3: J2.1, U1.12 (3V3)
+5V: J2.7, U1.14 (5V)
A0: R3.1, R4.2, U1.1 (D0/A0)
BASE: Q1.2 (B), R2.1
D2: R4.1, U1.3 (D2)
D6: R2.2, U1.7 (D6/TX)
D7: J2.3, U1.8 (D7/RX)
D8: J2.4, U1.9 (D8/SCK)
D9: J2.5, U1.10 (D9/MISO)
D10: J2.6, U1.11 (D10/MOSI)
GND: J1.2, J2.2, J2.8, Q1.3 (E), R3.2, U1.13 (GND)
LED_A: J3.1, R1.1
LED_K: J3.2, Q1.1 (C)
VBAT: J1.1, R1.2, U1.15 (VBAT)

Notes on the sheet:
UV-Sight carrier board for the XIAO nRF52840 Sense
UV LED driver: LED in the sight, 2-core wire to J3. LED runs from the battery (3.4-4.2 V), D6 PWM switches Q1. BC547 pinout (flat side facing you, legs down): C - B - E
Light sensor: D2 powers the LDR only during a measurement. LDR head sits in the hole in the housing floor.
Battery: LiPo 3.7 V 85 mAh with protection circuit. NTC wire: not connected, insulate. U1 pin 15 = short wire from the VBAT pad on the underside of the XIAO through the board.
J2: display / expansion (unused XIAO pins) 1 3V3 2 GND 3 D7 4 D8 (SCK) 5 D9 (MISO) 6 D10 (MOSI) 7 5V 8 GND
D1, D3, D4/SDA, D5/SCL stay free (reachable on the XIAO header pins).

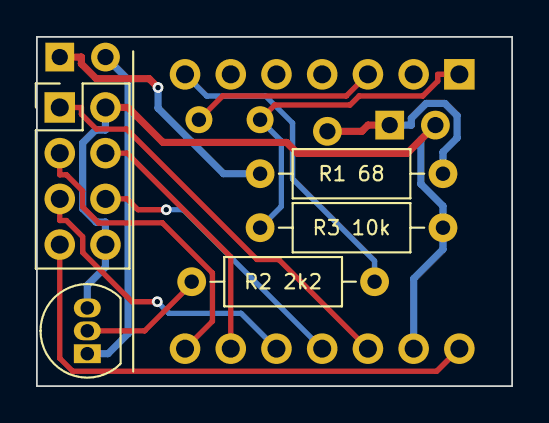
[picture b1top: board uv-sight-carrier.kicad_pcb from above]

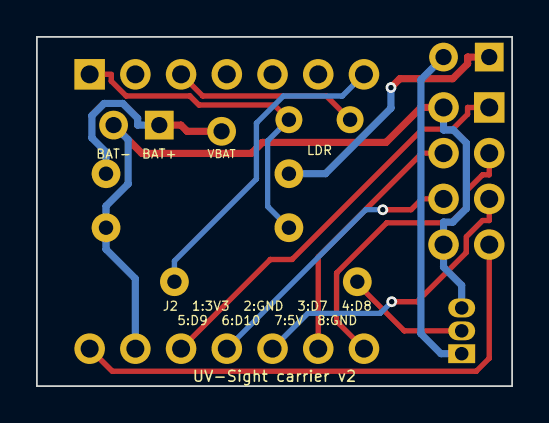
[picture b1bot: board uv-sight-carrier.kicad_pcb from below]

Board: 2 copper layers, 26.4 x 19.4 mm, 9 parts (2 on the bottom side), 14 nets.
